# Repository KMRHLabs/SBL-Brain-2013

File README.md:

# SBL Brain 2013

A PIC32 Microcontroller Based Dev Board

Note:
The hardware and software designs are covered under the Creative Commons Attribution-ShareAlike 4.0 International (CC BY-SA 4.0) lisence which means, you can pretty well do as you like with this project, so long as any new derivitaive works also have the same license and you keep us sited as the source of the design. 

The SBL Brain 2013 hardware and software design are "open source" projects, limitted only by a few 3rd party proprietary elements. In order to build the software, you will need to obtain some libraries that are not open source such as MicroChip's USB libraries. At the time of development, all 3rd party libraries and hardware have no licencing fee or royalty requirements. We are working towards a completely and truely open source project.

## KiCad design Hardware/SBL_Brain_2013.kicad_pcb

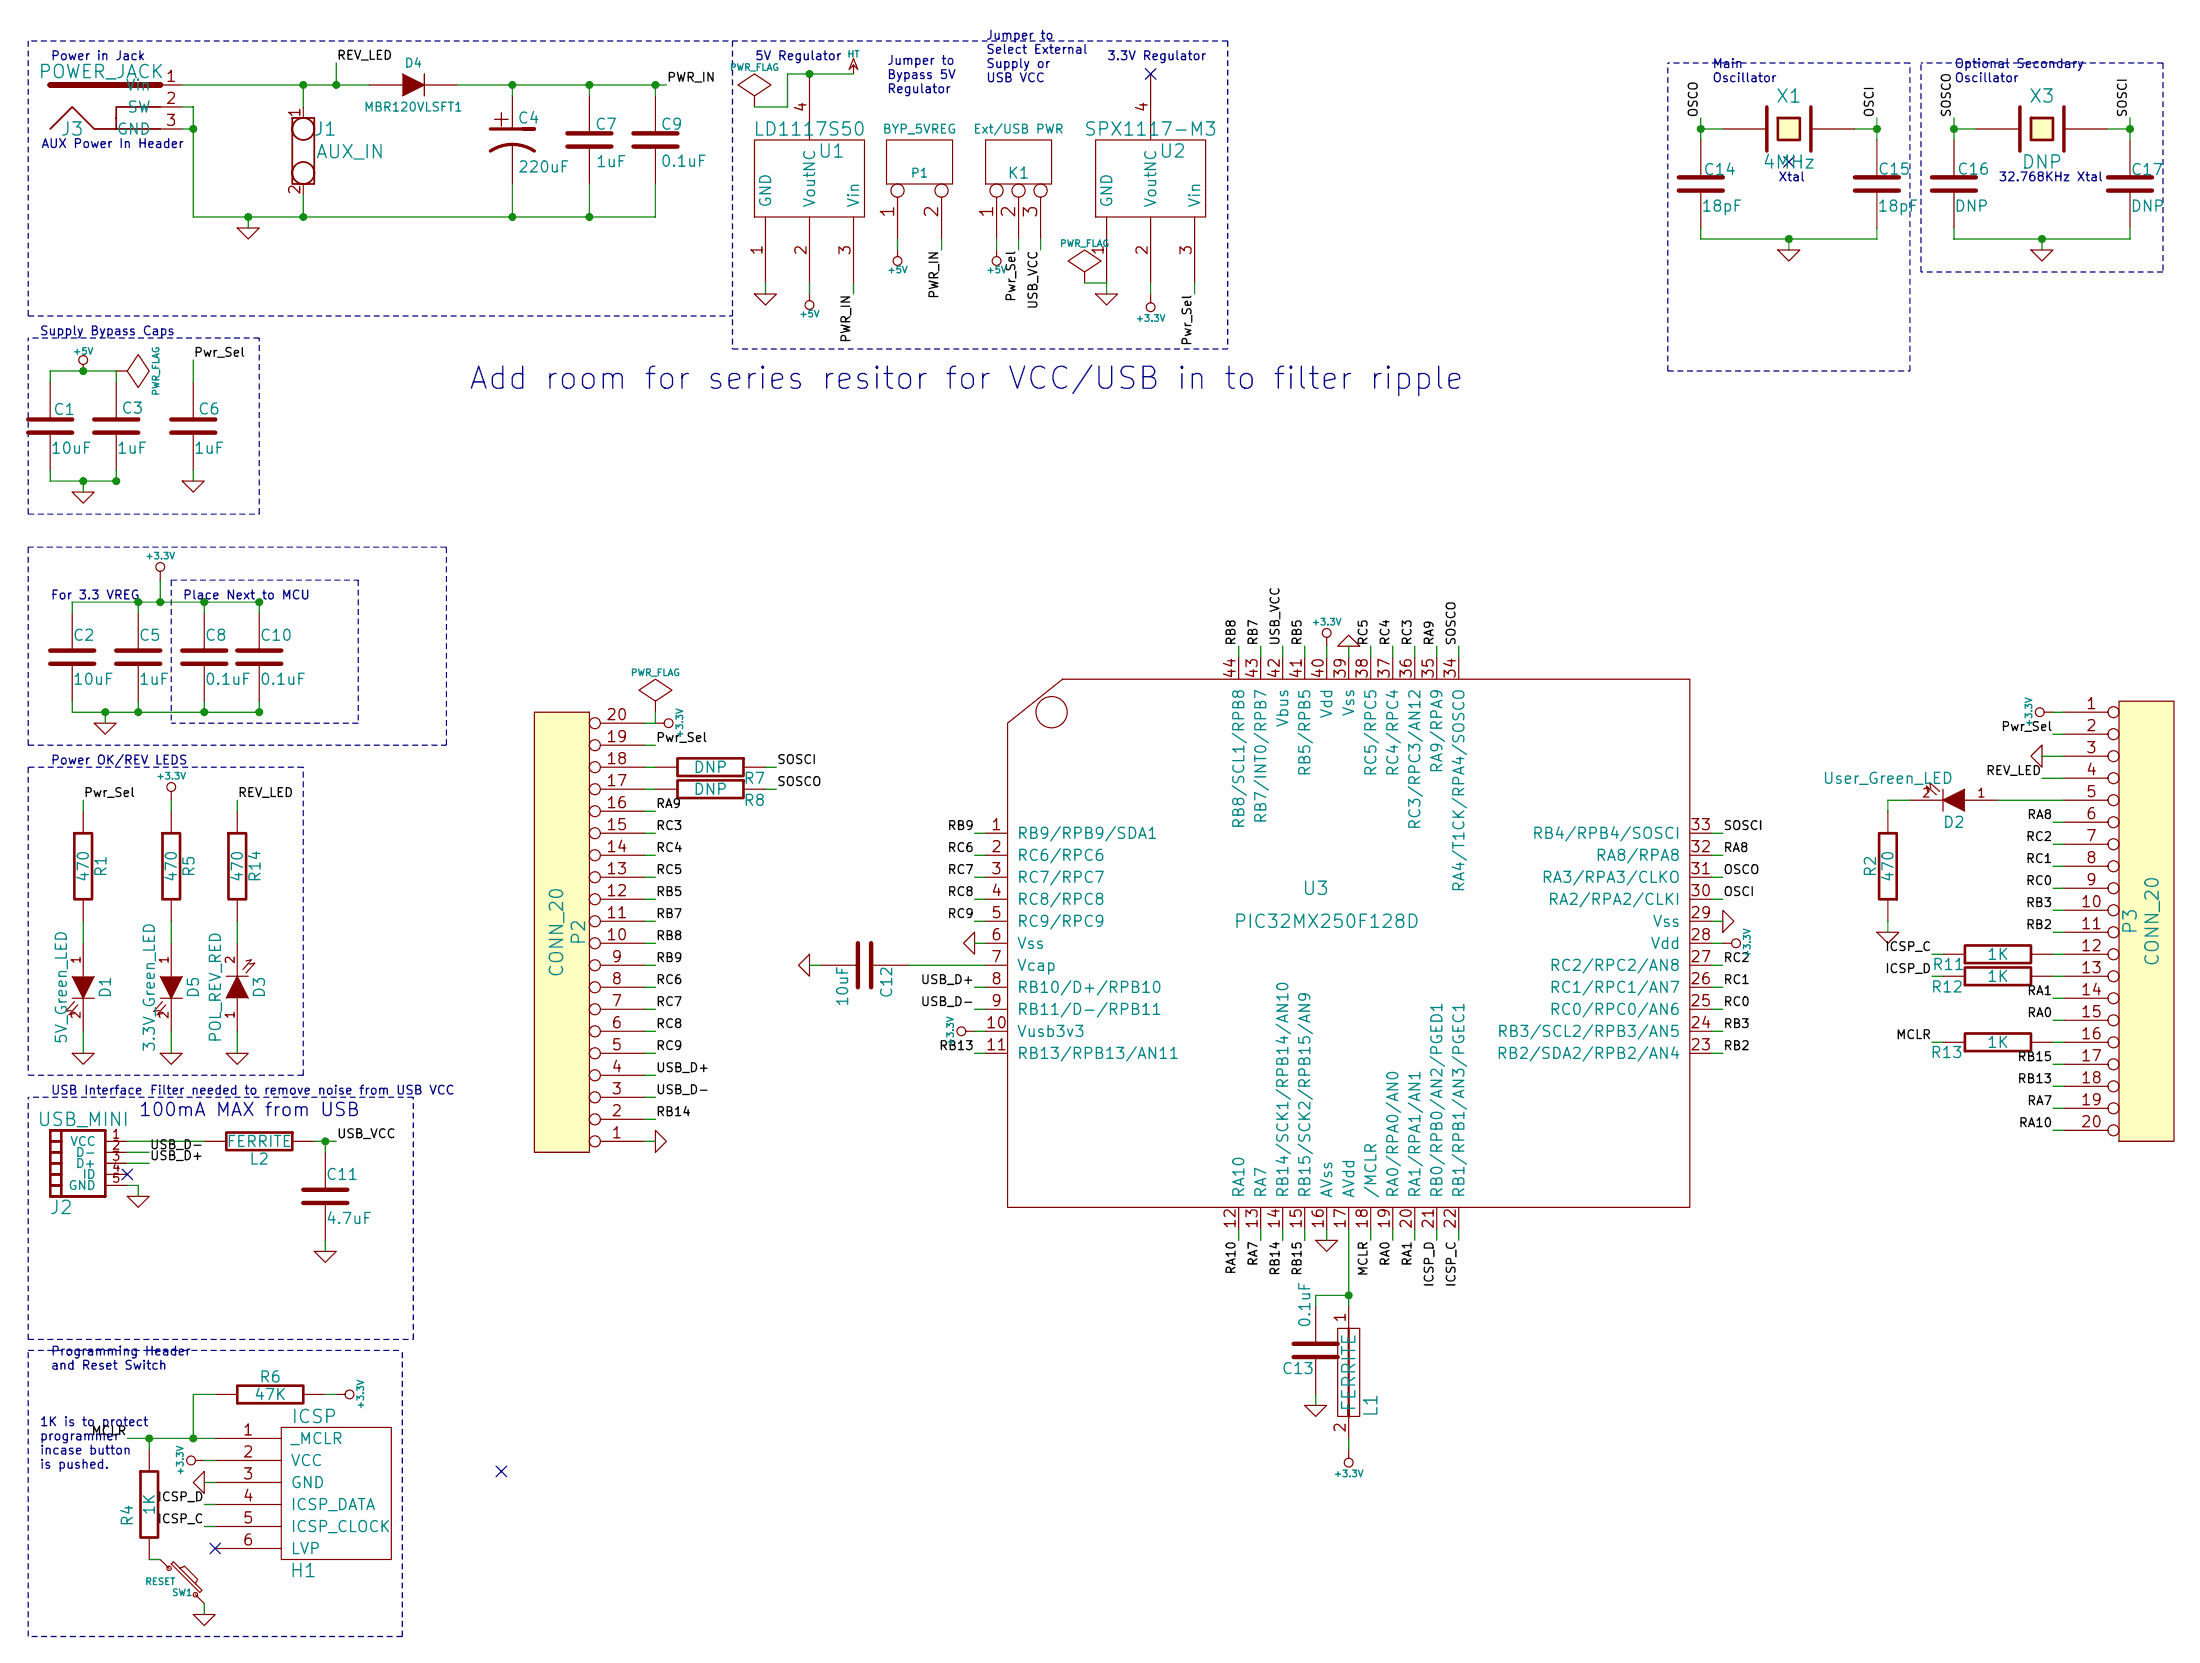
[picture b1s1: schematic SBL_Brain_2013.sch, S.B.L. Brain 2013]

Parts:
C1, C2, C12: 10uF
C3, C5, C6, C7: 1uF
C4: 220uF; Part Number B41827A4227M000; MouserPN 871-B41827A4227M000
C8, C9, C10, C13: 0.1uF
C11: 4.7uF
C14, C15: 18pF; Part Number GRM1885C1H180JA01D; MouserPN 81-GRM39C180J50
C16, C17: DNP
D1: 5V_Green_LED
D2: User_Green_LED
D3: POL_REV_RED
D4: MBR120VLSFT1
D5: 3.3V_Green_LED
H1: ICSP
J1: AUX_IN
J2: USB_MINI
J3: POWER_JACK
K1: Ext/USB PWR
L1, L2: FERRITE; Part Number LI0603E151R-10; MouserPN 875-LI0603E151R-10
P1: BYP_5VREG
P2, P3: CONN_20
R1, R2, R5, R14: 470
R4, R11, R12, R13: 1K
R6: 47K
R7, R8: DNP
SW1: RESET
U1: LD1117S50; Part Number LD1117S50TR
U2: SPX1117-M3; Part Number SPX1117M3-L-3-3; Mouser PN 701-SPX1117M3-L-3-3
U3: PIC32MX250F128D
X1: 4MHz; Part Number ABL-4.000MHZ-B2; MouserPN 815-ABL-4-B2
X3: DNP

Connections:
+3.3V: C2.1, C5.1, C8.1, C10.1, H1.2 (VCC), L1.2, P2.20, P3.1, R5.1, R6.2, U2.2 (Vout), U3.10 (Vusb3v3), U3.28 (Vdd), U3.40 (Vdd)
+5V: C1.1, C3.1, K1.1, P1.1, U1.2 (Vout)
/ICSP_C: H1.5 (ICSP_CLOCK), R11.1, U3.22 (RB1/RPB1/AN3/PGEC1)
/ICSP_D: H1.4 (ICSP_DATA), R12.1, U3.21 (RB0/RPB0/AN2/PGED1)
/MCLR: H1.1 (_MCLR), R4.1, R6.1, R13.1, U3.18 (/MCLR)
/OSCI: C15.1, U3.30 (RA2/RPA2/CLKI), X1.2
/OSCO: C14.1, U3.31 (RA3/RPA3/CLKO), X1.1
/PWR_IN: C4.1, C7.1, C9.1, D4.2 (K), P1.2 (PM), U1.3 (Vin)
/Pwr_Sel: C6.1, K1.2 (PM), P2.19, P3.2, R1.1, U2.3 (Vin)
/RA0: P3.15, U3.19 (RA0/RPA0/AN0)
/RA1: P3.14, U3.20 (RA1/RPA1/AN1)
/RA7: P3.19, U3.13 (RA7)
/RA8: P3.6, U3.32 (RA8/RPA8)
/RA9: P2.16, U3.35 (RA9/RPA9)
/RA10: P3.20, U3.12 (RA10)
/RB2: P3.11, U3.23 (RB2/SDA2/RPB2/AN4)
/RB3: P3.10, U3.24 (RB3/SCL2/RPB3/AN5)
/RB5: P2.12, U3.41 (RB5/RPB5)
/RB7: P2.11, U3.43 (RB7/INT0/RPB7)
/RB8: P2.10, U3.44 (RB8/SCL1/RPB8)
/RB9: P2.9, U3.1 (RB9/RPB9/SDA1)
/RB13: P3.18, U3.11 (RB13/RPB13/AN11)
/RB14: P2.2, U3.14 (RB14/SCK1/RPB14/AN10)
/RB15: P3.17, U3.15 (RB15/SCK2/RPB15/AN9)
/RC0: P3.9, U3.25 (RC0/RPC0/AN6)
/RC1: P3.8, U3.26 (RC1/RPC1/AN7)
/RC2: P3.7, U3.27 (RC2/RPC2/AN8)
/RC3: P2.15, U3.36 (RC3/RPC3/AN12)
/RC4: P2.14, U3.37 (RC4/RPC4)
/RC5: P2.13, U3.38 (RC5/RPC5)
/RC6: P2.8, U3.2 (RC6/RPC6)
/RC7: P2.7, U3.3 (RC7/RPC7)
/RC8: P2.6, U3.4 (RC8/RPC8)
/RC9: P2.5, U3.5 (RC9/RPC9)
/REV_LED: D4.1 (A), J1.1, J3.1 (Vin), P3.4, R14.1
/SOSCI: C17.1, R7.1, U3.33 (RB4/RPB4/SOSCI), X3.2
/SOSCO: C16.1, R8.1, U3.34 (RA4/T1CK/RPA4/SOSCO), X3.1
/USB_D+: J2.3 (D+), P2.4, U3.8 (RB10/D+/RPB10)
/USB_D-: J2.2 (D-), P2.3, U3.9 (RB11/D-/RPB11)
/USB_VCC: C11.1, K1.3, L2.1, U3.42 (Vbus)
GND: C1.2, C2.2, C3.2, C4.2, C5.2, C6.2, C7.2, C8.2, C9.2, C10.2, C11.2, C12.2, C13.2, C14.2, C15.2, C16.2, C17.2, D1.2 (K), D3.1 (A), D5.2 (K), H1.3 (GND), J1.2, J2.5 (GND), J3.2 (SW), J3.3 (GND), P2.1, P3.3, R2.1, SW1.2, U1.1 (GND), U2.1 (GND), U3.6 (Vss), U3.16 (AVss), U3.29 (Vss), U3.39 (Vss)
HT: U1.4 (NC)
unnamed: D2.1 (A), P3.5
unnamed: P3.16, R13.2
unnamed: P2.18, R7.2
unnamed: P2.17, R8.2
unnamed: P3.13, R12.2
unnamed: P3.12, R11.2
unnamed: D5.1 (A), R5.2
unnamed: D1.1 (A), R1.2
unnamed: R4.2, SW1.1
unnamed: C13.1, L1.1, U3.17 (AVdd)
unnamed: D3.2 (K), R14.2
unnamed: D2.2 (K), R2.2
unnamed: C12.1, U3.7 (Vcap)
unnamed: J2.1 (VCC), L2.2

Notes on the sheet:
100mA MAX from USB
Filter needed to remove noise from USB VCC
Add room for series resitor for VCC/USB in to filter ripple
For 3.3 VREG
Jumper to Select External Supply or USB VCC
USB Interface
1K is to protect programmer incase button is pushed.
Place Next to MCU
32.768KHz Xtal
Xtal
Optional Secondary Oscillator
Main Oscillator
Programming Header and Reset Switch
3.3V Regulator
Jumper to Bypass 5V Regulator
5V Regulator
AUX Power In Header
Power in Jack
Power OK/REV LEDS
Supply Bypass Caps

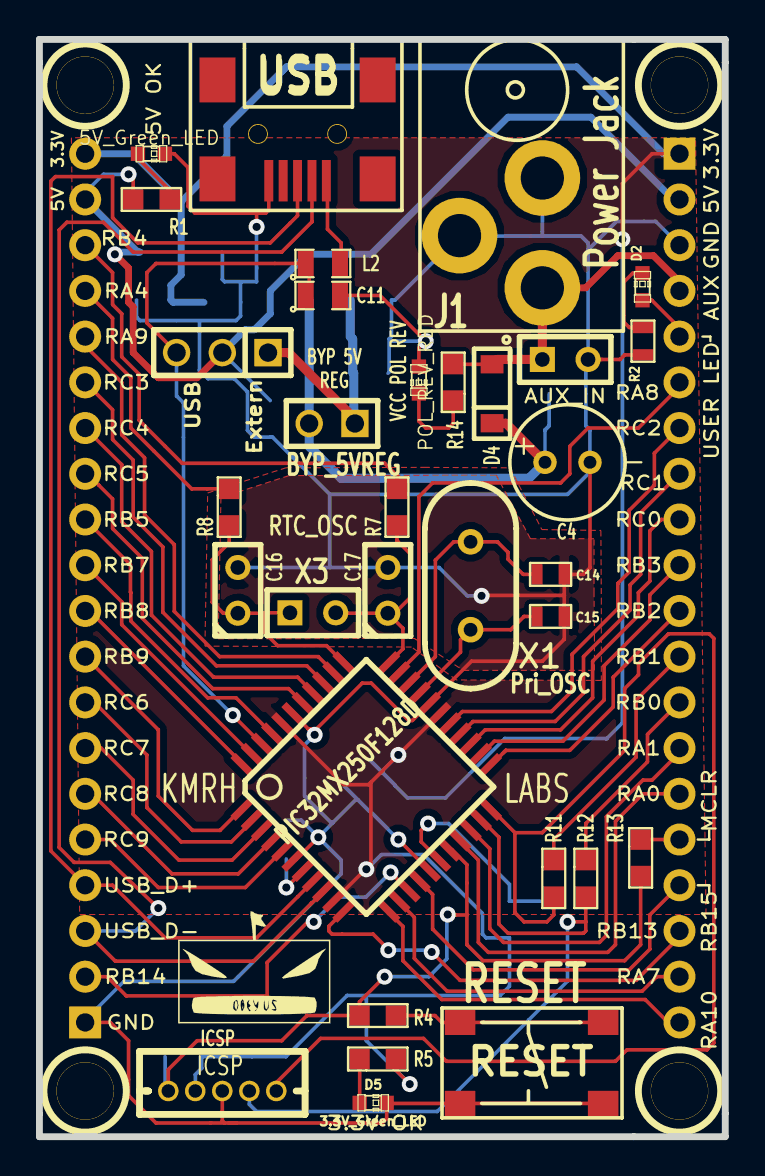
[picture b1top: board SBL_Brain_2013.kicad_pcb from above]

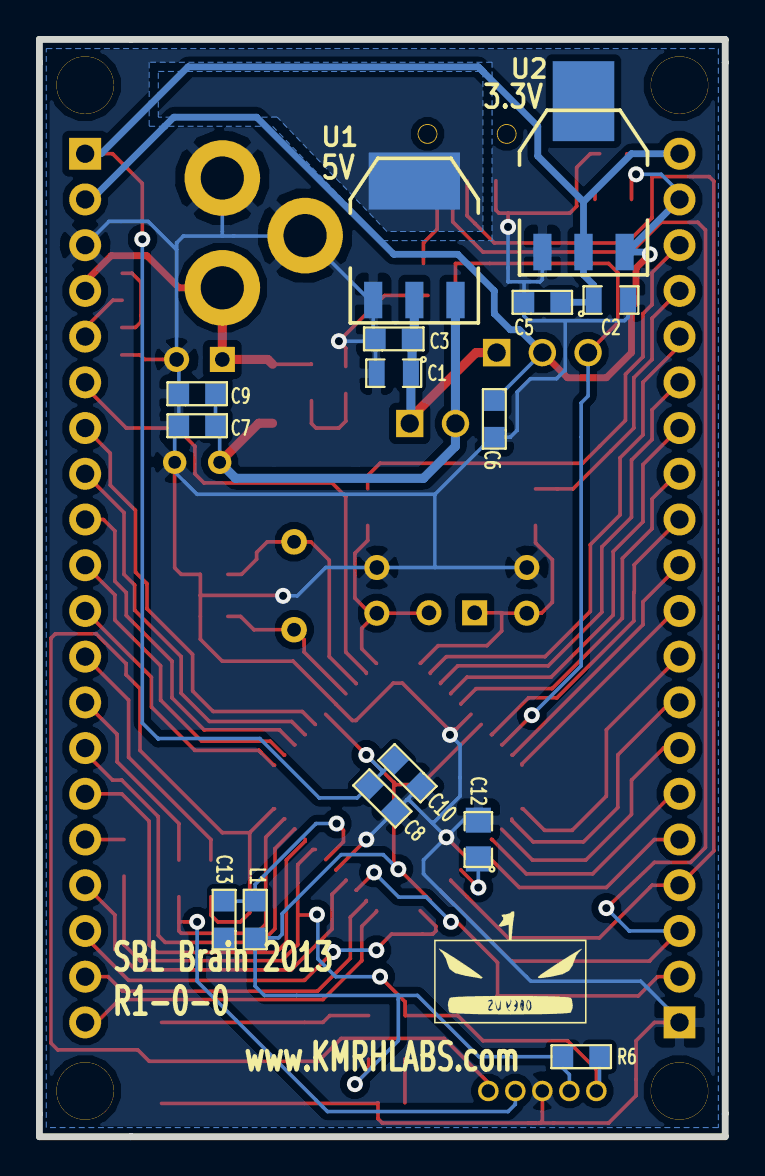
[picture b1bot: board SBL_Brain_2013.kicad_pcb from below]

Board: 2 copper layers, 38.1 x 61.0 mm, 53 parts (15 on the bottom side), 55 nets.

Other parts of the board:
4-40, 4-40#2, 4-40#3, 4-40#4: P***; 1pin

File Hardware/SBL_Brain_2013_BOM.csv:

Id	Designator	Package	Quantity	Designation	Supplier and ref
1	C11	SM0805	1	4.7uF	
2	C12,C2,C1	SM0805	3	10uF	
3	C3,C5,C6,C7	SM0603	4	1uF	
4	C4	CP_R_2.5mm	1	220uF	
5	C8,C9,C10,C13	SM0603	4	0.1uF	
6	D1	LED-0603	1	5V_Green_LED	
7	D2	LED-0603	1	User_Green_LED	
8	D3	LED-0603	1	POL_REV_RED	
9	D4	SOD-123	1	MBR120VLSFT1	
10	D5	LED-0603	1	3.3V_Green_LED	
11	J2	USB_MINI_SMD	1	USB_MINI	
12	J3	Power_Jack_2.1mm	1	POWER_JACK	
13	K1	SIL-3	1	Ext/USB_PWR	
14	L1	SM0603	1	FERRITE	
15	L2	SM0805	1	FERRITE	
16	P1	SIL-2	1	BYP_5VREG	
17	P2,P3	SIL-20	2	CONN_20	
18	R13,R12,R11,R4	SM0603	4	1K	
19	R5,R1,R14,R2	SM0603	4	470	
20	R6	SM0603	1	47K	
21	SW1	SW_6MM_SMD	1	RESET	
22	U1	SOT223	1	LD1117S50	
23	U2	SOT223	1	SPX1117-M3	
24	U3	TQFP44	1	PIC32MX250F128D	
25	C15,C14	SM0603	2	DNP	
26	C16,C17	C1	2	DNP	
27	H1	ICSP_1.5MM_Mini	1	DNP	
28	J1	SIL-2	1	DNP	
29	R8,R7	SM0603	2	DNP	User option. DNP for Ext Osc.
30	X1	HC-49US	1	DNP	
31	X3	SIL-2	1	DNP

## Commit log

2015-04-05 :neckbeard: Added .gitattributes & .gitignore files
2015-04-05 Intial GitHub Sync
